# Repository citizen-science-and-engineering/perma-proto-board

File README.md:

### Perma prototype board

Similar to a breadboard but more friendly to I2C and SPI.

#### Perma proto board v1

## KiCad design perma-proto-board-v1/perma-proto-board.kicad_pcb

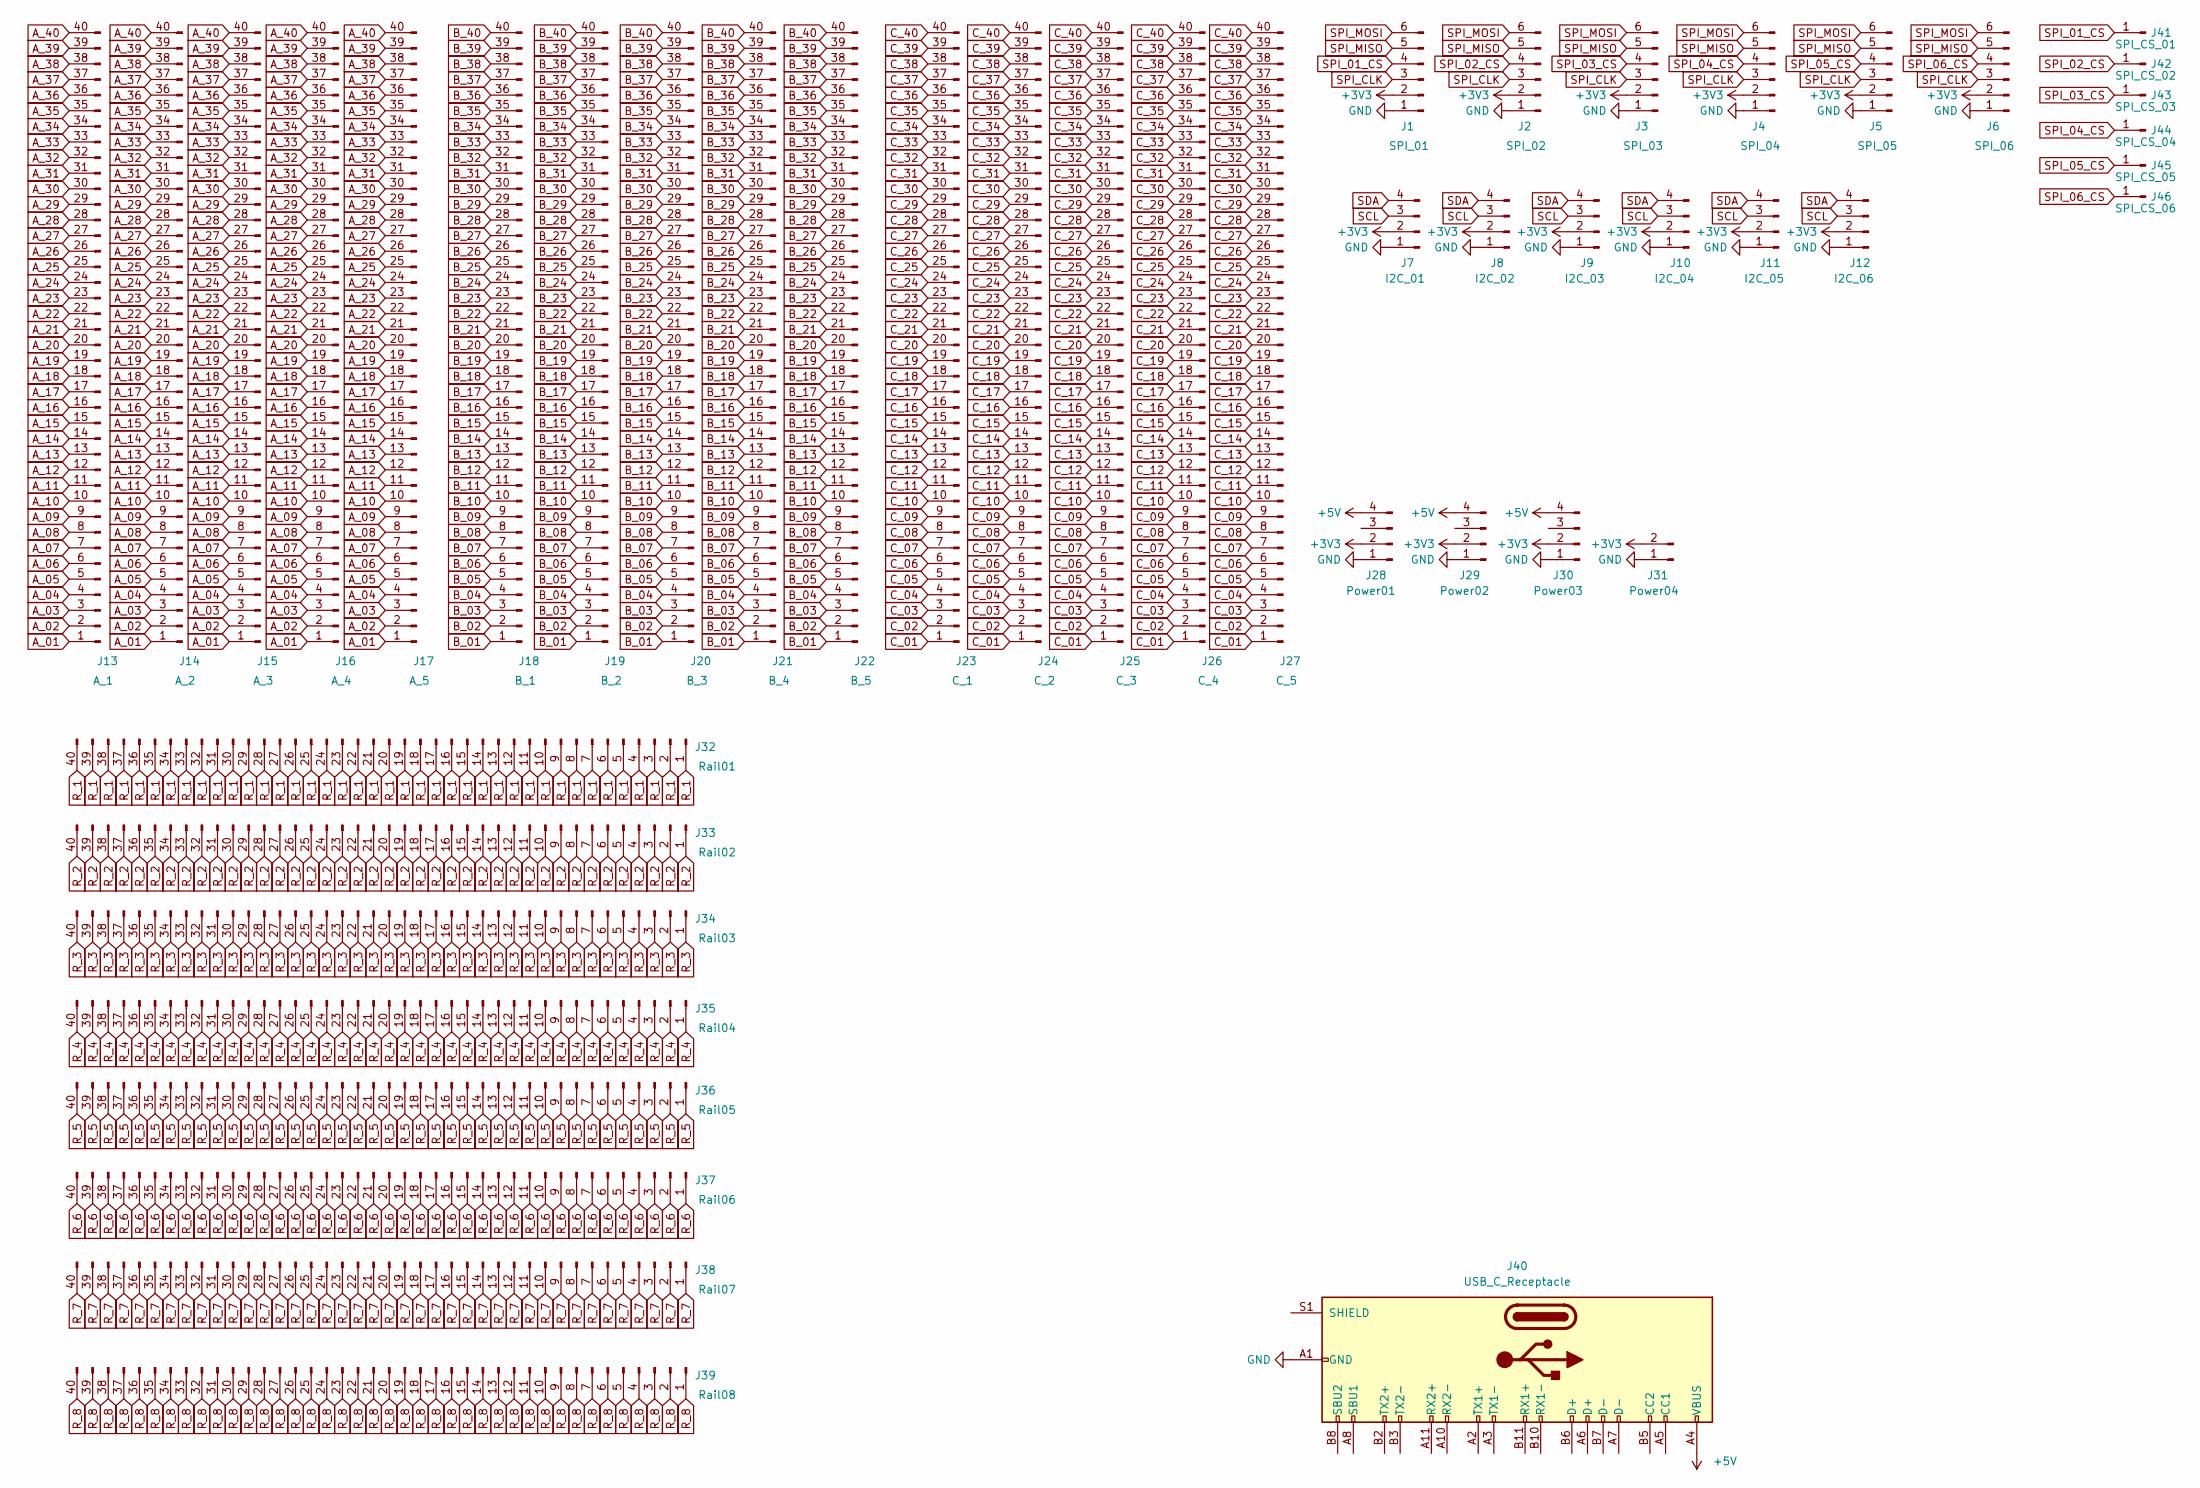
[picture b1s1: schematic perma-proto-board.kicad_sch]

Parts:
J1: SPI_01; PinHeader_1x06_P2.54mm_Vertical
J2: SPI_02; PinHeader_1x06_P2.54mm_Vertical
J3: SPI_03; PinHeader_1x06_P2.54mm_Vertical
J4: SPI_04; PinHeader_1x06_P2.54mm_Vertical
J5: SPI_05; PinHeader_1x06_P2.54mm_Vertical
J6: SPI_06; PinHeader_1x06_P2.54mm_Vertical
J7: I2C_01; PinHeader_1x04_P2.54mm_Vertical
J8: I2C_02; PinHeader_1x04_P2.54mm_Vertical
J9: I2C_03; PinHeader_1x04_P2.54mm_Vertical
J10: I2C_04; PinHeader_1x04_P2.54mm_Vertical
J11: I2C_05; PinHeader_1x04_P2.54mm_Vertical
J12: I2C_06; PinHeader_1x04_P2.54mm_Vertical
J13: A_1; PinHeader_1x40_P2.54mm_Vertical_NO_Silk
J14: A_2; PinHeader_1x40_P2.54mm_Vertical_NO_Silk
J15: A_3; PinHeader_1x40_P2.54mm_Vertical_NO_Silk
J16: A_4; PinHeader_1x40_P2.54mm_Vertical_NO_Silk
J17: A_5; PinHeader_1x40_P2.54mm_Vertical_NO_Silk
J18: B_1; PinHeader_1x40_P2.54mm_Vertical_NO_Silk
J19: B_2; PinHeader_1x40_P2.54mm_Vertical_NO_Silk
J20: B_3; PinHeader_1x40_P2.54mm_Vertical_NO_Silk
J21: B_4; PinHeader_1x40_P2.54mm_Vertical_NO_Silk
J22: B_5; PinHeader_1x40_P2.54mm_Vertical_NO_Silk
J23: C_1; PinHeader_1x40_P2.54mm_Vertical_NO_Silk
J24: C_2; PinHeader_1x40_P2.54mm_Vertical_NO_Silk
J25: C_3; PinHeader_1x40_P2.54mm_Vertical_NO_Silk
J26: C_4; PinHeader_1x40_P2.54mm_Vertical_NO_Silk
J27: C_5; PinHeader_1x40_P2.54mm_Vertical_NO_Silk
J28: Power01; PinHeader_1x04_P2.54mm_Vertical
J29: Power02; PinHeader_1x04_P2.54mm_Vertical
J30: Power03; PinHeader_1x04_P2.54mm_Vertical
J31: Power04; PinHeader_1x02_P2.54mm_Vertical
J32: Rail01; PinHeader_1x40_P2.54mm_Vertical
J33: Rail02; PinHeader_1x40_P2.54mm_Vertical
J34: Rail03; PinHeader_1x40_P2.54mm_Vertical
J35: Rail04; PinHeader_1x40_P2.54mm_Vertical
J36: Rail05; PinHeader_1x40_P2.54mm_Vertical
J37: Rail06; PinHeader_1x40_P2.54mm_Vertical
J38: Rail07; PinHeader_1x40_P2.54mm_Vertical
J39: Rail08; PinHeader_1x40_P2.54mm_Vertical
J40: USB_C_Receptacle; USB_C_Receptacle_HRO_TYPE-C-31-M-12
J41: SPI_CS_01; PinHeader_1x01_P2.54mm_Vertical
J42: SPI_CS_02; PinHeader_1x01_P2.54mm_Vertical
J43: SPI_CS_03; PinHeader_1x01_P2.54mm_Vertical
J44: SPI_CS_04; PinHeader_1x01_P2.54mm_Vertical
J45: SPI_CS_05; PinHeader_1x01_P2.54mm_Vertical
J46: SPI_CS_06; PinHeader_1x01_P2.54mm_Vertical

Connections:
+3V3: J1.2, J2.2, J3.2, J4.2, J5.2, J6.2, J7.2, J8.2, J9.2, J10.2, J11.2, J12.2, J28.2, J29.2, J30.2, J31.2
+5V: J28.4, J29.4, J30.4, J40.A4 (VBUS), J40.A9 (VBUS), J40.B4 (VBUS), J40.B9 (VBUS)
A_01: J13.1, J14.1, J15.1, J16.1, J17.1
A_02: J13.2, J14.2, J15.2, J16.2, J17.2
A_03: J13.3, J14.3, J15.3, J16.3, J17.3
A_04: J13.4, J14.4, J15.4, J16.4, J17.4
A_05: J13.5, J14.5, J15.5, J16.5, J17.5
A_06: J13.6, J14.6, J15.6, J16.6, J17.6
A_07: J13.7, J14.7, J15.7, J16.7, J17.7
A_08: J13.8, J14.8, J15.8, J16.8, J17.8
A_09: J13.9, J14.9, J15.9, J16.9, J17.9
A_10: J13.10, J14.10, J15.10, J16.10, J17.10
A_11: J13.11, J14.11, J15.11, J16.11, J17.11
A_12: J13.12, J14.12, J15.12, J16.12, J17.12
A_13: J13.13, J14.13, J15.13, J16.13, J17.13
A_14: J13.14, J14.14, J15.14, J16.14, J17.14
A_15: J13.15, J14.15, J15.15, J16.15, J17.15
A_16: J13.16, J14.16, J15.16, J16.16, J17.16
A_17: J13.17, J14.17, J15.17, J16.17, J17.17
A_18: J13.18, J14.18, J15.18, J16.18, J17.18
A_19: J13.19, J14.19, J15.19, J16.19, J17.19
A_20: J13.20, J14.20, J15.20, J16.20, J17.20
A_21: J13.21, J14.21, J15.21, J16.21, J17.21
A_22: J13.22, J14.22, J15.22, J16.22, J17.22
A_23: J13.23, J14.23, J15.23, J16.23, J17.23
A_24: J13.24, J14.24, J15.24, J16.24, J17.24
A_25: J13.25, J14.25, J15.25, J16.25, J17.25
A_26: J13.26, J14.26, J15.26, J16.26, J17.26
A_27: J13.27, J14.27, J15.27, J16.27, J17.27
A_28: J13.28, J14.28, J15.28, J16.28, J17.28
A_29: J13.29, J14.29, J15.29, J16.29, J17.29
A_30: J13.30, J14.30, J15.30, J16.30, J17.30
A_31: J13.31, J14.31, J15.31, J16.31, J17.31
A_32: J13.32, J14.32, J15.32, J16.32, J17.32
A_33: J13.33, J14.33, J15.33, J16.33, J17.33
A_34: J13.34, J14.34, J15.34, J16.34, J17.34
A_35: J13.35, J14.35, J15.35, J16.35, J17.35
A_36: J13.36, J14.36, J15.36, J16.36, J17.36
A_37: J13.37, J14.37, J15.37, J16.37, J17.37
A_38: J13.38, J14.38, J15.38, J16.38, J17.38
A_39: J13.39, J14.39, J15.39, J16.39, J17.39
A_40: J13.40, J14.40, J15.40, J16.40, J17.40
B_01: J18.1, J19.1, J20.1, J21.1, J22.1
B_02: J18.2, J19.2, J20.2, J21.2, J22.2
B_03: J18.3, J19.3, J20.3, J21.3, J22.3
B_04: J18.4, J19.4, J20.4, J21.4, J22.4
B_05: J18.5, J19.5, J20.5, J21.5, J22.5
B_06: J18.6, J19.6, J20.6, J21.6, J22.6
B_07: J18.7, J19.7, J20.7, J21.7, J22.7
B_08: J18.8, J19.8, J20.8, J21.8, J22.8
B_09: J18.9, J19.9, J20.9, J21.9, J22.9
B_10: J18.10, J19.10, J20.10, J21.10, J22.10
B_11: J18.11, J19.11, J20.11, J21.11, J22.11
B_12: J18.12, J19.12, J20.12, J21.12, J22.12
B_13: J18.13, J19.13, J20.13, J21.13, J22.13
B_14: J18.14, J19.14, J20.14, J21.14, J22.14
B_15: J18.15, J19.15, J20.15, J21.15, J22.15
B_16: J18.16, J19.16, J20.16, J21.16, J22.16
B_17: J18.17, J19.17, J20.17, J21.17, J22.17
B_18: J18.18, J19.18, J20.18, J21.18, J22.18
B_19: J18.19, J19.19, J20.19, J21.19, J22.19
B_20: J18.20, J19.20, J20.20, J21.20, J22.20
B_21: J18.21, J19.21, J20.21, J21.21, J22.21
B_22: J18.22, J19.22, J20.22, J21.22, J22.22
B_23: J18.23, J19.23, J20.23, J21.23, J22.23
B_24: J18.24, J19.24, J20.24, J21.24, J22.24
B_25: J18.25, J19.25, J20.25, J21.25, J22.25
B_26: J18.26, J19.26, J20.26, J21.26, J22.26
B_27: J18.27, J19.27, J20.27, J21.27, J22.27
B_28: J18.28, J19.28, J20.28, J21.28, J22.28
B_29: J18.29, J19.29, J20.29, J21.29, J22.29
B_30: J18.30, J19.30, J20.30, J21.30, J22.30
B_31: J18.31, J19.31, J20.31, J21.31, J22.31
B_32: J18.32, J19.32, J20.32, J21.32, J22.32
B_33: J18.33, J19.33, J20.33, J21.33, J22.33
B_34: J18.34, J19.34, J20.34, J21.34, J22.34
B_35: J18.35, J19.35, J20.35, J21.35, J22.35
B_36: J18.36, J19.36, J20.36, J21.36, J22.36
B_37: J18.37, J19.37, J20.37, J21.37, J22.37
B_38: J18.38, J19.38, J20.38, J21.38, J22.38
B_39: J18.39, J19.39, J20.39, J21.39, J22.39
B_40: J18.40, J19.40, J20.40, J21.40, J22.40
C_01: J23.1, J24.1, J25.1, J26.1, J27.1
C_02: J23.2, J24.2, J25.2, J26.2, J27.2
C_03: J23.3, J24.3, J25.3, J26.3, J27.3
C_04: J23.4, J24.4, J25.4, J26.4, J27.4
C_05: J23.5, J24.5, J25.5, J26.5, J27.5
C_06: J23.6, J24.6, J25.6, J26.6, J27.6
C_07: J23.7, J24.7, J25.7, J26.7, J27.7
C_08: J23.8, J24.8, J25.8, J26.8, J27.8
C_09: J23.9, J24.9, J25.9, J26.9, J27.9
C_10: J23.10, J24.10, J25.10, J26.10, J27.10
C_11: J23.11, J24.11, J25.11, J26.11, J27.11
C_12: J23.12, J24.12, J25.12, J26.12, J27.12
C_13: J23.13, J24.13, J25.13, J26.13, J27.13
C_14: J23.14, J24.14, J25.14, J26.14, J27.14
C_15: J23.15, J24.15, J25.15, J26.15, J27.15
C_16: J23.16, J24.16, J25.16, J26.16, J27.16
C_17: J23.17, J24.17, J25.17, J26.17, J27.17
C_18: J23.18, J24.18, J25.18, J26.18, J27.18
C_19: J23.19, J24.19, J25.19, J26.19, J27.19
C_20: J23.20, J24.20, J25.20, J26.20, J27.20
C_21: J23.21, J24.21, J25.21, J26.21, J27.21
C_22: J23.22, J24.22, J25.22, J26.22, J27.22
C_23: J23.23, J24.23, J25.23, J26.23, J27.23
C_24: J23.24, J24.24, J25.24, J26.24, J27.24
C_25: J23.25, J24.25, J25.25, J26.25, J27.25
C_26: J23.26, J24.26, J25.26, J26.26, J27.26
C_27: J23.27, J24.27, J25.27, J26.27, J27.27
C_28: J23.28, J24.28, J25.28, J26.28, J27.28
C_29: J23.29, J24.29, J25.29, J26.29, J27.29
C_30: J23.30, J24.30, J25.30, J26.30, J27.30
C_31: J23.31, J24.31, J25.31, J26.31, J27.31
C_32: J23.32, J24.32, J25.32, J26.32, J27.32
C_33: J23.33, J24.33, J25.33, J26.33, J27.33
C_34: J23.34, J24.34, J25.34, J26.34, J27.34
C_35: J23.35, J24.35, J25.35, J26.35, J27.35
C_36: J23.36, J24.36, J25.36, J26.36, J27.36
C_37: J23.37, J24.37, J25.37, J26.37, J27.37
C_38: J23.38, J24.38, J25.38, J26.38, J27.38
C_39: J23.39, J24.39, J25.39, J26.39, J27.39
C_40: J23.40, J24.40, J25.40, J26.40, J27.40
GND: J1.1, J2.1, J3.1, J4.1, J5.1, J6.1, J7.1, J8.1, J9.1, J10.1, J11.1, J12.1, J28.1, J29.1, J30.1, J31.1, J40.A1 (GND), J40.A12 (GND), J40.B1 (GND), J40.B12 (GND)
R_1: J32.1, J32.2, J32.3, J32.4, J32.5, J32.6, J32.7, J32.8, J32.9, J32.10, J32.11, J32.12, J32.13, J32.14, J32.15, J32.16, J32.17, J32.18, J32.19, J32.20, J32.21, J32.22, J32.23, J32.24, J32.25, J32.26, J32.27, J32.28, J32.29, J32.30, J32.31, J32.32, J32.33, J32.34, J32.35, J32.36, J32.37, J32.38, J32.39, J32.40
R_2: J33.1, J33.2, J33.3, J33.4, J33.5, J33.6, J33.7, J33.8, J33.9, J33.10, J33.11, J33.12, J33.13, J33.14, J33.15, J33.16, J33.17, J33.18, J33.19, J33.20, J33.21, J33.22, J33.23, J33.24, J33.25, J33.26, J33.27, J33.28, J33.29, J33.30, J33.31, J33.32, J33.33, J33.34, J33.35, J33.36, J33.37, J33.38, J33.39, J33.40
R_3: J34.1, J34.2, J34.3, J34.4, J34.5, J34.6, J34.7, J34.8, J34.9, J34.10, J34.11, J34.12, J34.13, J34.14, J34.15, J34.16, J34.17, J34.18, J34.19, J34.20, J34.21, J34.22, J34.23, J34.24, J34.25, J34.26, J34.27, J34.28, J34.29, J34.30, J34.31, J34.32, J34.33, J34.34, J34.35, J34.36, J34.37, J34.38, J34.39, J34.40
R_4: J35.1, J35.2, J35.3, J35.4, J35.5, J35.6, J35.7, J35.8, J35.9, J35.10, J35.11, J35.12, J35.13, J35.14, J35.15, J35.16, J35.17, J35.18, J35.19, J35.20, J35.21, J35.22, J35.23, J35.24, J35.25, J35.26, J35.27, J35.28, J35.29, J35.30, J35.31, J35.32, J35.33, J35.34, J35.35, J35.36, J35.37, J35.38, J35.39, J35.40
R_5: J36.1, J36.2, J36.3, J36.4, J36.5, J36.6, J36.7, J36.8, J36.9, J36.10, J36.11, J36.12, J36.13, J36.14, J36.15, J36.16, J36.17, J36.18, J36.19, J36.20, J36.21, J36.22, J36.23, J36.24, J36.25, J36.26, J36.27, J36.28, J36.29, J36.30, J36.31, J36.32, J36.33, J36.34, J36.35, J36.36, J36.37, J36.38, J36.39, J36.40
R_6: J37.1, J37.2, J37.3, J37.4, J37.5, J37.6, J37.7, J37.8, J37.9, J37.10, J37.11, J37.12, J37.13, J37.14, J37.15, J37.16, J37.17, J37.18, J37.19, J37.20, J37.21, J37.22, J37.23, J37.24, J37.25, J37.26, J37.27, J37.28, J37.29, J37.30, J37.31, J37.32, J37.33, J37.34, J37.35, J37.36, J37.37, J37.38, J37.39, J37.40
R_7: J38.1, J38.2, J38.3, J38.4, J38.5, J38.6, J38.7, J38.8, J38.9, J38.10, J38.11, J38.12, J38.13, J38.14, J38.15, J38.16, J38.17, J38.18, J38.19, J38.20, J38.21, J38.22, J38.23, J38.24, J38.25, J38.26, J38.27, J38.28, J38.29, J38.30, J38.31, J38.32, J38.33, J38.34, J38.35, J38.36, J38.37, J38.38, J38.39, J38.40
R_8: J39.1, J39.2, J39.3, J39.4, J39.5, J39.6, J39.7, J39.8, J39.9, J39.10, J39.11, J39.12, J39.13, J39.14, J39.15, J39.16, J39.17, J39.18, J39.19, J39.20, J39.21, J39.22, J39.23, J39.24, J39.25, J39.26, J39.27, J39.28, J39.29, J39.30, J39.31, J39.32, J39.33, J39.34, J39.35, J39.36, J39.37, J39.38, J39.39, J39.40
SCL: J7.3, J8.3, J9.3, J10.3, J11.3, J12.3
SDA: J7.4, J8.4, J9.4, J10.4, J11.4, J12.4
SPI_01_CS: J1.4, J41.1
SPI_02_CS: J2.4, J42.1
SPI_03_CS: J3.4, J43.1
SPI_04_CS: J4.4, J44.1
SPI_05_CS: J5.4, J45.1
SPI_06_CS: J6.4, J46.1
SPI_CLK: J1.3, J2.3, J3.3, J4.3, J5.3, J6.3
SPI_MISO: J1.5, J2.5, J3.5, J4.5, J5.5, J6.5
SPI_MOSI: J1.6, J2.6, J3.6, J4.6, J5.6, J6.6

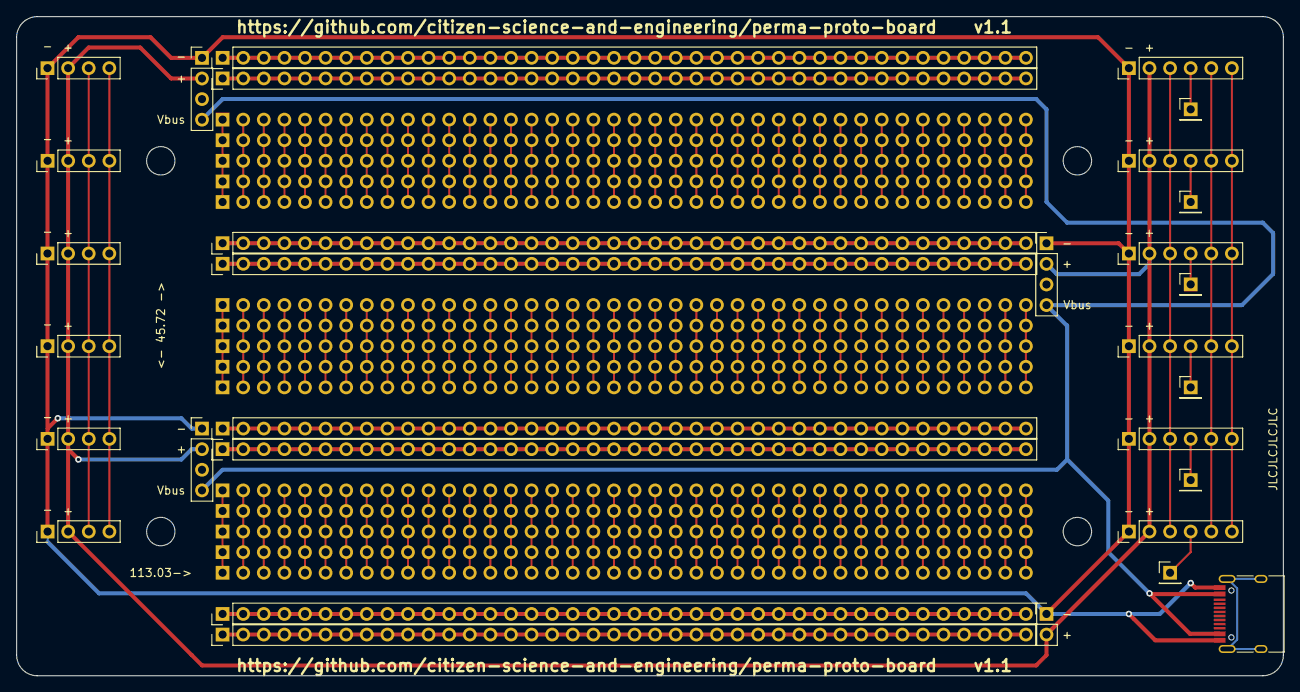
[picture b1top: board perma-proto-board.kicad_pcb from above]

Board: 2 copper layers, 156.2 x 81.3 mm, 46 parts (0 on the bottom side), 142 nets.

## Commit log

2022-02-22 initial design
2022-02-22 image
2022-02-22 subfolder
2022-02-22 added github url to silk screen
2022-02-22 Added silk screen to back of pcb
2022-02-23 v1.1
2022-02-23 silk screen fix
